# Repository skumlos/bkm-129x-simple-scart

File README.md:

The BKM-129X compatible with SCART instead of BNC.

Including a mono mixing circuit from SCART audio to RCA out, for monitors with internal audio in from option cards.

3D printable bracket here: https://www.thingiverse.com/thing:4460188

Requires Arduino Nano v3.0 loaded with the software from https://github.com/skumlos/bkm-129x-mcu

Revision history:

B: Fixed THS7374 filter bypass, change to Kicad 5

A: Initial revision

Copyright © 2020 Martin Hejnfelt <martin@hejnfelt.com>
This work is free. You can redistribute it and/or modify it under the
terms of the Do What The Fuck You Want To Public License, Version 2,
as published by Sam Hocevar. See the LICENSE file for more details.

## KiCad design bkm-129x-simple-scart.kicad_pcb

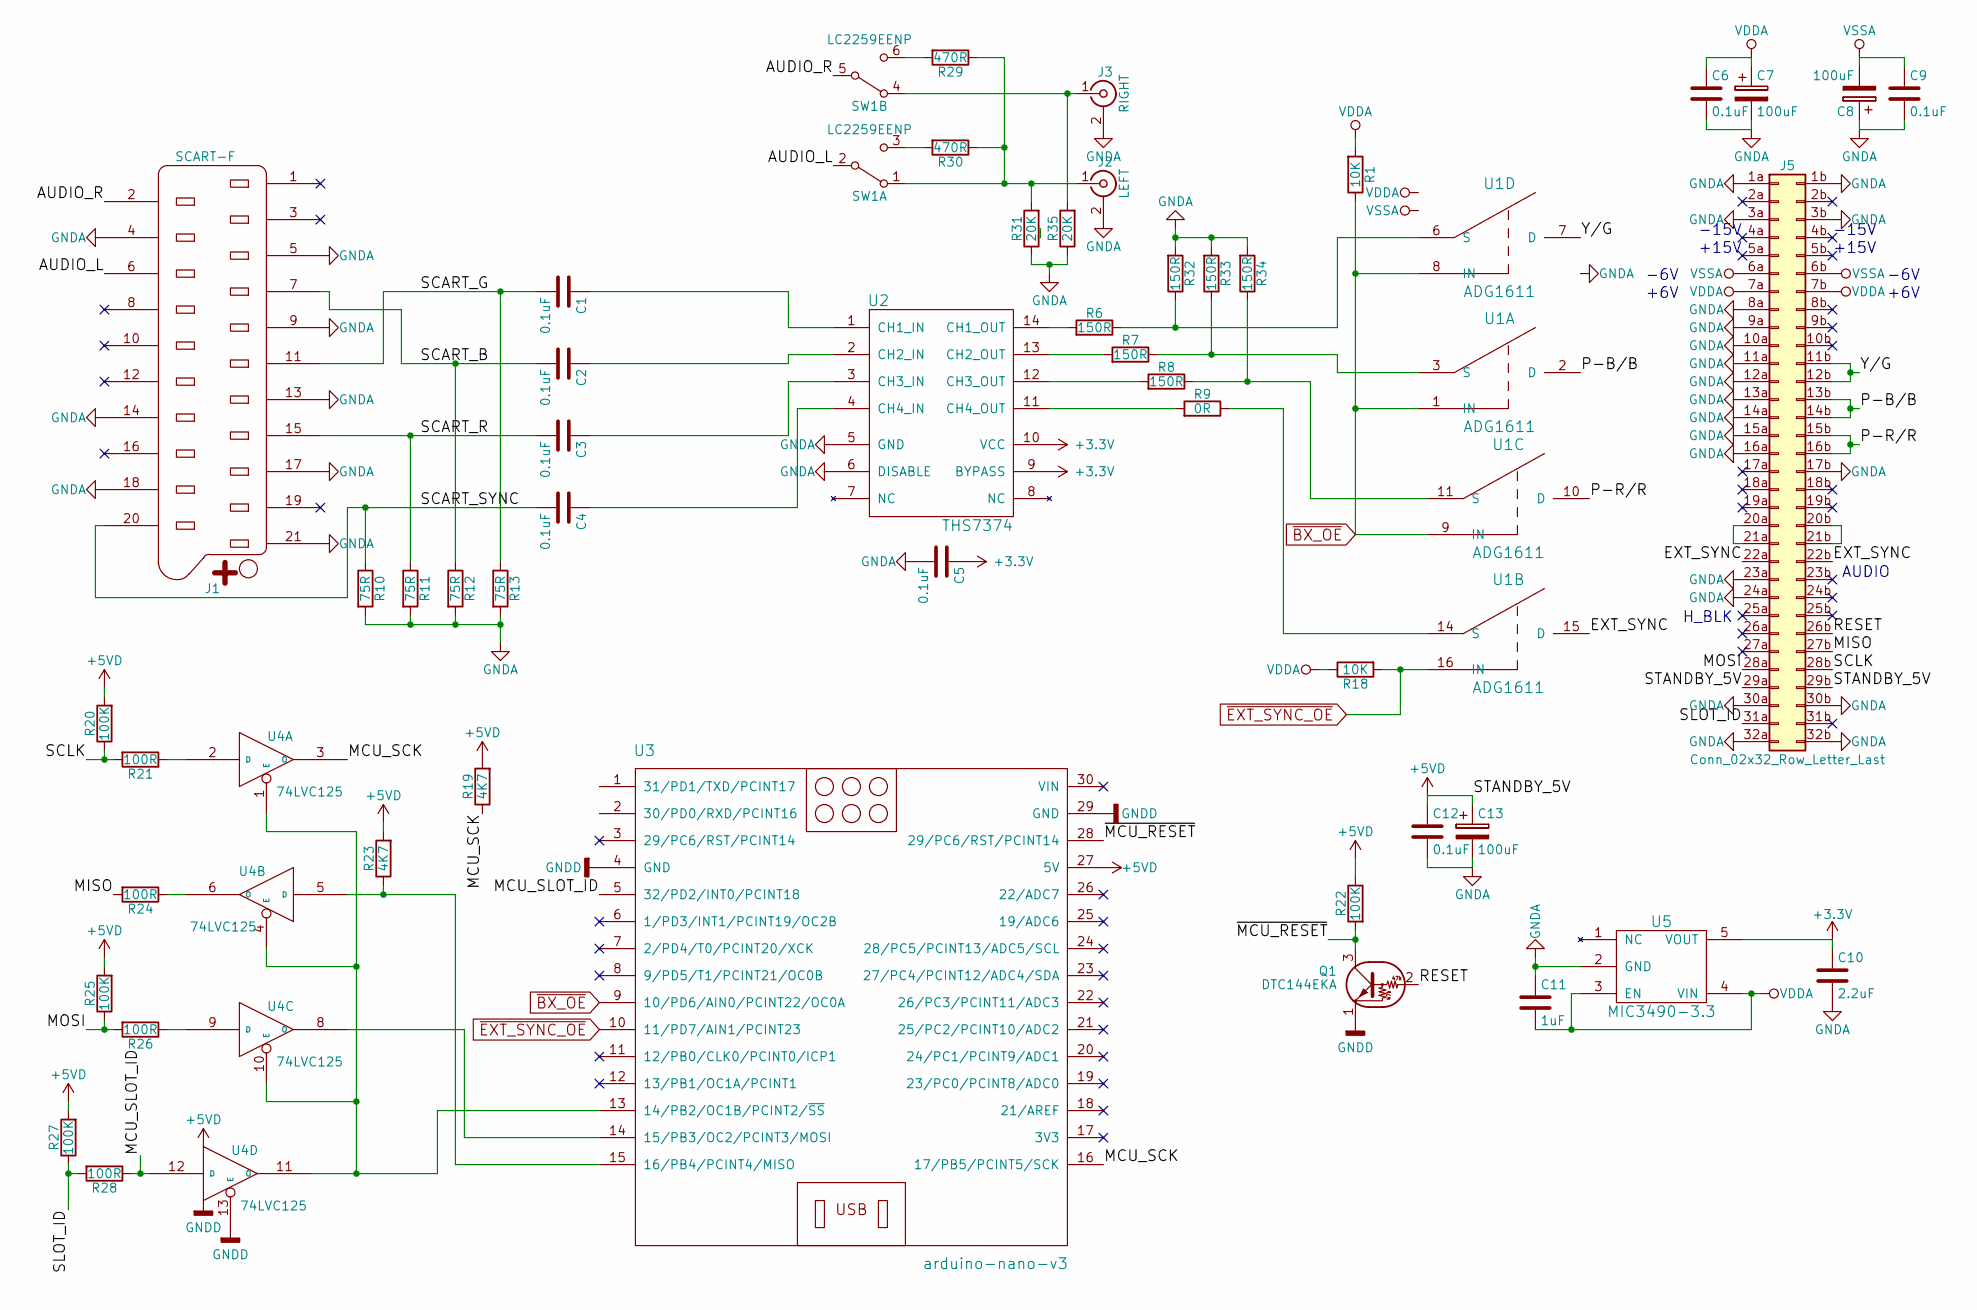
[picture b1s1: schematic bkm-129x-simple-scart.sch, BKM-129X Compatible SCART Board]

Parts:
C1, C2, C3, C4, C5, C6, C9, C12: 0.1uF; C_0805_HandSoldering
C7, C8, C13: 100uF; CP_Elec_6.3x5.3
C10: 2.2uF; C_0805_HandSoldering
C11: 1uF; C_0805_HandSoldering
J1: SCART-F; NINIGI-SCART-RA
J2: LEFT; RCJ-04X
J3: RIGHT; RCJ-04X
J5: Conn_02x32_Row_Letter_Last; DIN-41612-64P
Q1: DTC144EKA; SC-59_Handsoldering
R1, R18: 10K; R_0805_HandSoldering
R6, R7, R8, R32, R33, R34: 150R; R_0805_HandSoldering
R9: 0R; R_0805_HandSoldering
R10, R11, R12, R13: 75R; R_0805_HandSoldering
R19, R23: 4K7; R_0805_HandSoldering
R20, R22, R25, R27: 100K; R_0805_HandSoldering
R21, R24, R26, R28: 100R; R_0805_HandSoldering
R29, R30: 470R; R_0805_HandSoldering
R31, R35: 20K; R_0805_HandSoldering
SW1: LC2259EENP; LC2259
U1: ADG1611; TSSOP-16_4.4x5mm_Pitch0.65mm
U2: THS7374; TSSOP-14_4.4x5mm_Pitch0.65mm
U3: arduino-nano-v3
U4: 74LVC125; TSSOP-14_4.4x5mm_Pitch0.65mm
U5: MIC3490-3.3; SOT-23-5_HandSoldering

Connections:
+3V3: C5.1, C10.1, U2.9 (BYPASS), U2.10 (VCC), U5.5 (VOUT)
+5VD: C12.1, C13.1, J5.29a, J5.29b, R19.2, R20.2, R22.1, R23.2, R25.2, R27.2, U3.27 (5V), U4.14 (VCC)
/AUDIO_L: J1.6, SW1.2 (B)
/AUDIO_R: J1.2, SW1.5 (B)
/EXT_SYNC: J5.22a, J5.22b, U1.15 (D)
/MCU_SCK: R19.1, U3.16 (17/PB5/PCINT5/SCK), U4.3 (O)
/MCU_SLOT_ID: R28.1, U3.5 (32/PD2/INT0/PCINT18), U4.12 (D)
/MISO: J5.27b, R24.2
/MOSI: J5.28a, R25.1, R26.2
/P-B/B: J5.13b, J5.14b, U1.2 (D)
/P-R/R: J5.15b, J5.16b, U1.10 (D)
/RESET: J5.26b, Q1.2 (B)
/SCART_B: C2.2, J1.7, R12.1
/SCART_G: C1.2, J1.11, R13.1
/SCART_R: C3.2, J1.15, R11.1
/SCART_SYNC: C4.2, J1.20, R10.1
/SCLK: J5.28b, R20.1, R21.2
/SLOT_ID: J5.31a, R27.1, R28.2
/Y/G: J5.11b, J5.12b, U1.7 (D)
/~MCU_RESET: Q1.3 (C), R22.2, U3.28 (29/PC6/RST/PCINT14)
unnamed: C1.1, U2.1 (CH1_IN)
unnamed: C2.1, U2.2 (CH2_IN)
unnamed: C3.1, U2.3 (CH3_IN)
unnamed: C4.1, U2.4 (CH4_IN)
unnamed: J2.1 (In), R29.1, R30.1, R31.2, SW1.1 (A)
unnamed: J3.1 (In), R35.2, SW1.4 (A)
unnamed: J5.20a, J5.21a
unnamed: J5.20b, J5.21b
unnamed: R6.2, U2.14 (CH1_OUT)
unnamed: R7.2, U2.13 (CH2_OUT)
unnamed: R8.2, U2.12 (CH3_OUT)
unnamed: R9.1, U1.14 (S)
unnamed: R9.2, U2.11 (CH4_OUT)
unnamed: R21.1, U4.2 (D)
unnamed: R23.1, U3.15 (16/PB4/PCINT4/MISO), U4.5 (D)
unnamed: R24.1, U4.6 (O)
unnamed: R26.1, U4.9 (D)
unnamed: R29.2, SW1.6 (C)
unnamed: R30.2, SW1.3 (C)
unnamed: R6.1, R32.1, U1.6 (S)
unnamed: R7.1, R33.1, U1.3 (S)
unnamed: R8.1, R34.1, U1.11 (S)
unnamed: U3.13 (14/PB2/OC1B/PCINT2/~SS), U4.1 (E), U4.4 (E), U4.10 (E), U4.11 (O)
unnamed: U3.14 (15/PB3/OC2/PCINT3/MOSI), U4.8 (O)
VDD: C6.1, C7.1, C11.2, J5.7a, J5.7b, R1.2, R18.1, U1.13 (VDD), U5.3 (EN), U5.4 (VIN)
VSS: C8.2, C9.1, J5.6a, J5.6b, U1.4 (VSS)
~BX_OE: R1.1, U1.1 (IN), U1.8 (IN), U1.9 (IN), U3.9 (10/PD6/AIN0/PCINT22/OC0A)
~EXT_SYNC_OE: R18.2, U1.16 (IN), U3.10 (11/PD7/AIN1/PCINT23)

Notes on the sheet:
-15V
+15V
-6V
+6V
AUDIO
H_BLK

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
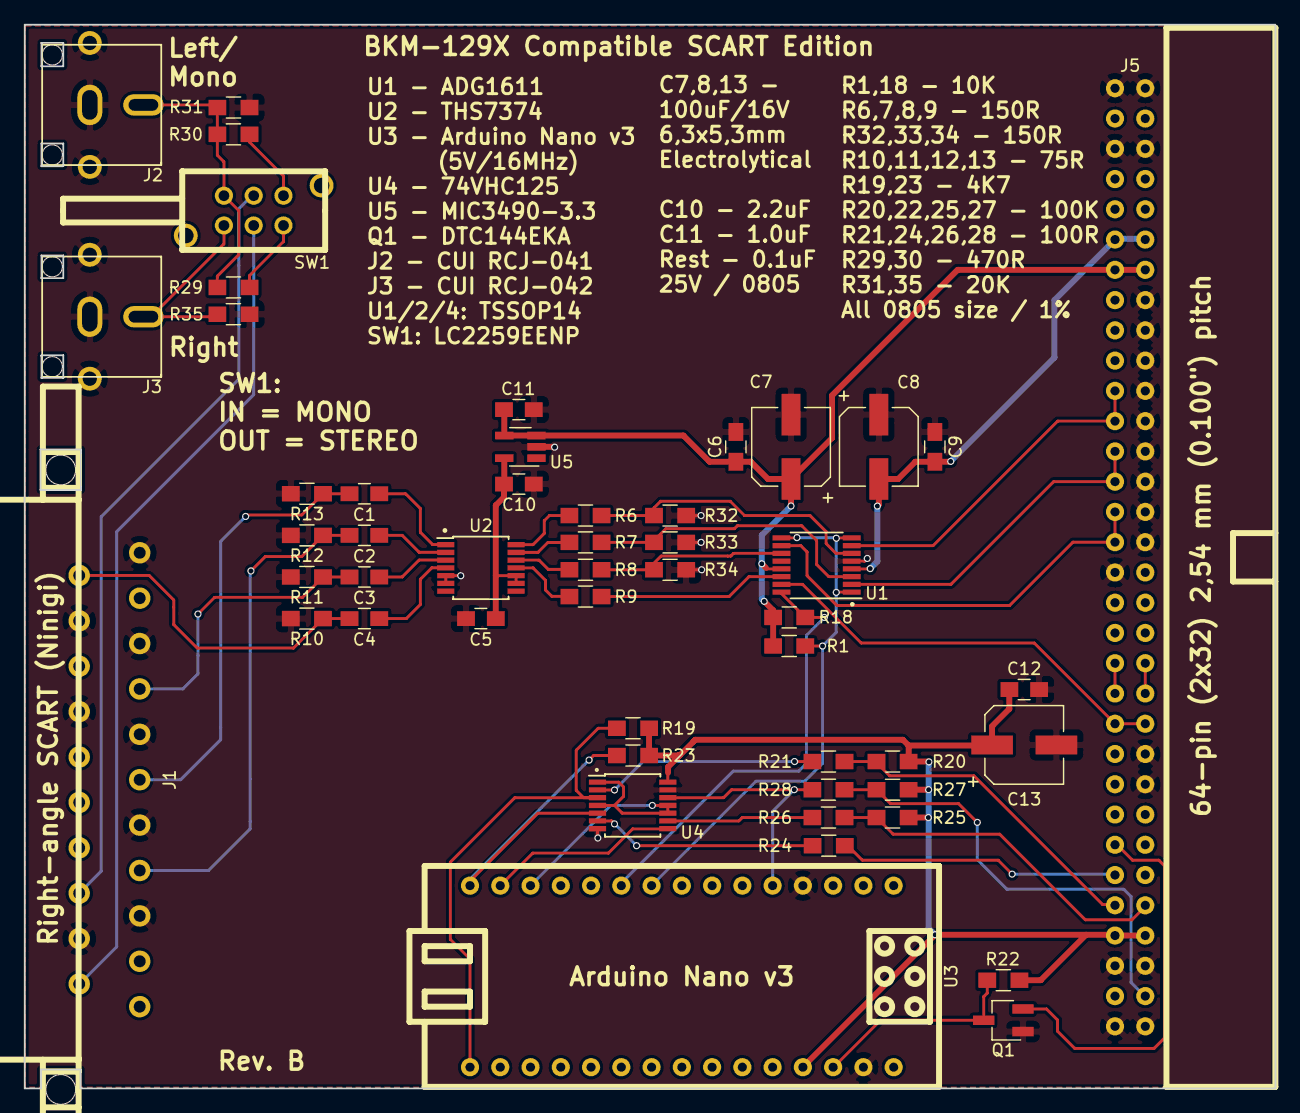
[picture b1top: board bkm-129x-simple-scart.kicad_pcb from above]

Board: 2 copper layers, 105.0 x 89.3 mm, 51 parts (0 on the bottom side), 49 nets.

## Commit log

2020-03-01 Fixed some footprints
2020-03-01 Fixed SCART pad size and added signal names
2020-06-13 Added audio switch, enlarge holes for SCART fasteners
2020-06-13 Added cache
2020-06-14 Fixed erroneous RCA plug part number
2020-06-19 Aligned partslist text
2020-07-24 Add license info
2021-05-09 Revision B
